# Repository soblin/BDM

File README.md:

Repository for development of "Electrical Informtion Processing Devices"

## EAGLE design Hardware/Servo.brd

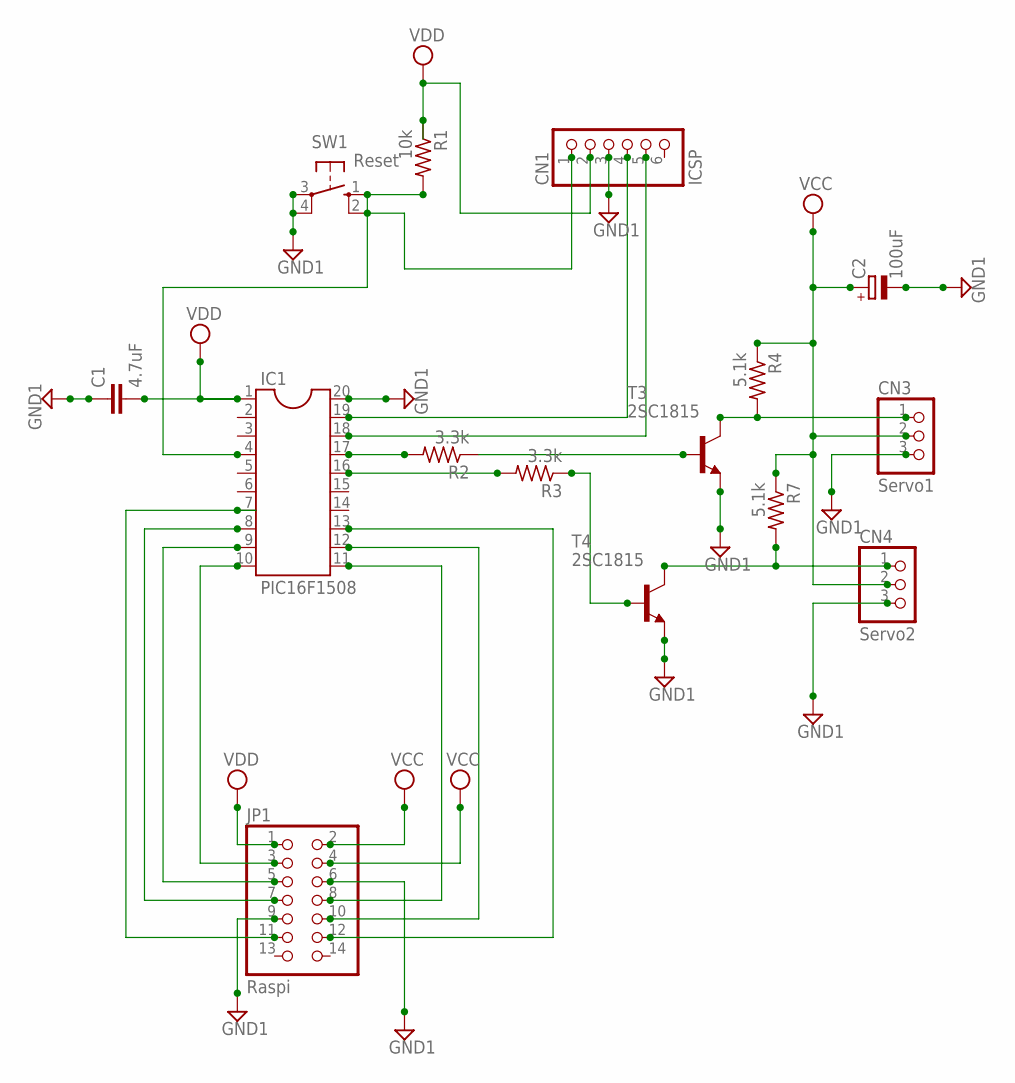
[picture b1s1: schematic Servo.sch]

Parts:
C1: 4.7uF; C025-025X050
C2: 100uF; PANASONIC_A
CN1: ICSP; 1X06
CN3: Servo1; 1X03
CN4: Servo2; 1X03
IC1: PIC16F1508; SOCKET-20
JP1: Raspi; 2X07
R1: 10k; V526-0
R2, R3: 3.3k; V526-0
R4, R7: 5.1k; V526-0
SW1: Reset; B3F-10XX
T3, T4: 2SC1815; TO92-ECB

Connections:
GND1: C1.1, C2.-, CN1.3, CN3.3, CN4.3, IC1.20, JP1.6, JP1.9, SW1.3, SW1.4 (P1), T3.E, T4.E
unnamed: IC1.10, JP1.3
unnamed: IC1.9, JP1.5
unnamed: IC1.8, JP1.7
unnamed: CN4.1, R7.2, T4.C
unnamed: IC1.7, JP1.11
unnamed: IC1.11, JP1.8
unnamed: IC1.12, JP1.10
unnamed: CN1.1, IC1.4, R1.2, SW1.1 (S), SW1.2 (S1)
unnamed: IC1.13, JP1.12
unnamed: IC1.17, R2.2
unnamed: IC1.16, R3.2
unnamed: R2.1, T3.B
unnamed: R3.1, T4.B
unnamed: CN3.1, R4.2, T3.C
unnamed: CN1.4, IC1.19
unnamed: CN1.5, IC1.18
VCC: C2.+, CN3.2, CN4.2, JP1.2, JP1.4, R4.1, R7.1
VDD: C1.2, CN1.2, IC1.1, JP1.1, R1.1

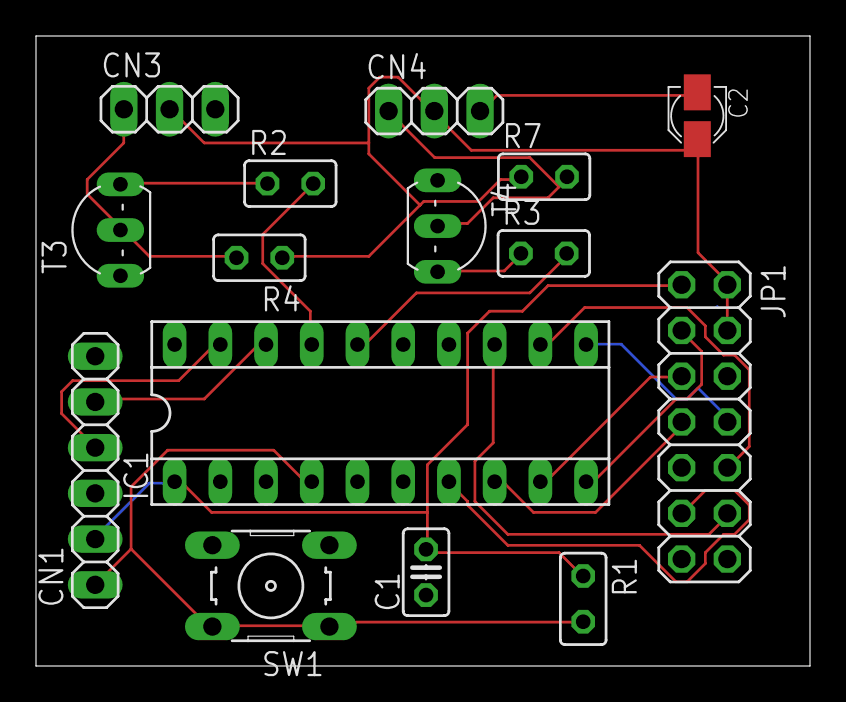
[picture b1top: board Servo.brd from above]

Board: 2 copper layers, 43.0 x 35.0 mm, 15 parts (0 on the bottom side), 19 nets.

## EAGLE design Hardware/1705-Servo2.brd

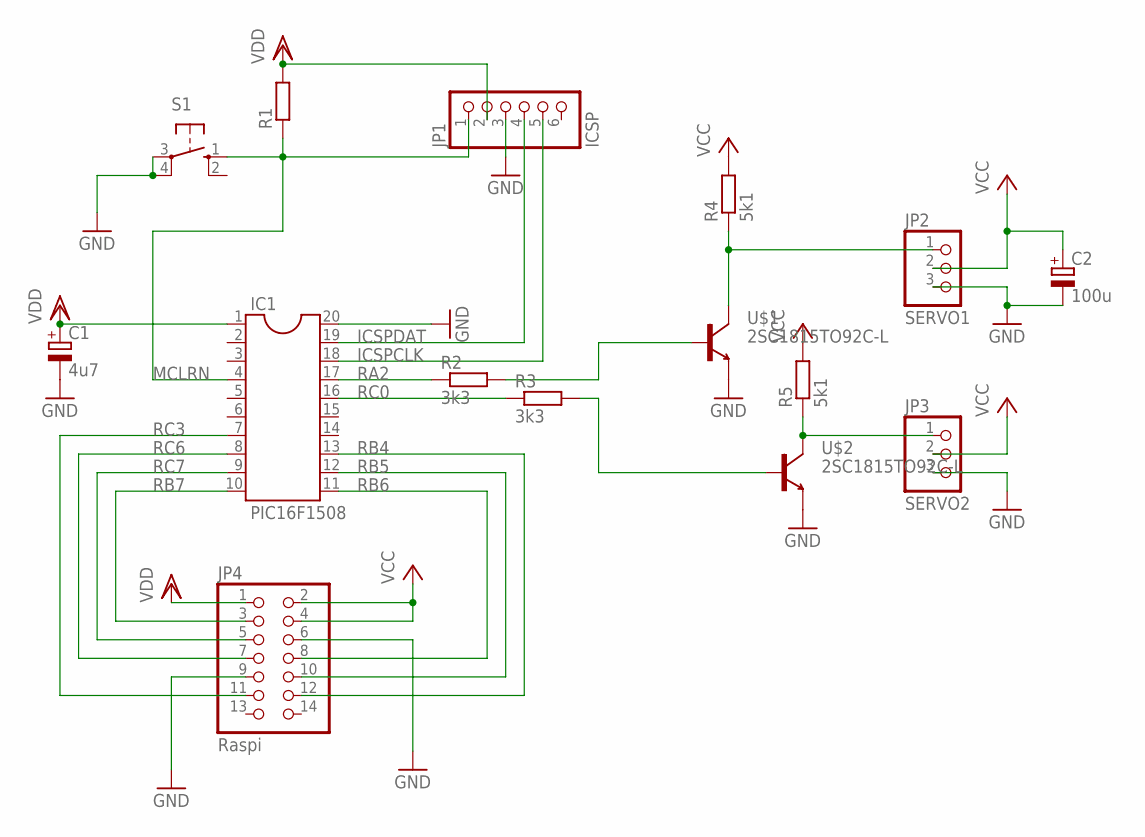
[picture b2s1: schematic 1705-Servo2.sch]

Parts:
C1: 4u7; E5-6E
C2: 100u; E2,5-6E
IC1: PIC16F1508; DIL20
JP1: ICSP; 1X06
JP2: SERVO1; 1X03
JP3: SERVO2; 1X03
JP4: Raspi; 2X07
R1: R-EU_0207/2V; 0207/2V
R2, R3: 3k3; 0204/8
R4, R5: 5k1; 0207/2V
S1: 10-XX; B3F-10XX
U$1, U$2: 2SC1815TO92C-L; TO92C-L

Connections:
GND: C1.-, C2.-, IC1.20, JP1.3, JP2.3, JP3.3, JP4.6, JP4.9, S1.3, S1.4 (P1), U$1.1 (E), U$2.1 (E)
ICSPCLK: IC1.18, JP1.5
ICSPDAT: IC1.19, JP1.4
MCLRN: IC1.4, JP1.1, R1.1, S1.1 (S)
unnamed: JP2.1, R4.1, U$1.2 (C)
unnamed: JP3.1, R5.1, U$2.2 (C)
unnamed: R2.2, U$1.3 (B)
unnamed: R3.2, U$2.3 (B)
RA2: IC1.17, R2.1
RB4: IC1.13, JP4.12
RB5: IC1.12, JP4.10
RB6: IC1.11, JP4.8
RB7: IC1.10, JP4.3
RC0: IC1.16, R3.1
RC3: IC1.7, JP4.11
RC6: IC1.8, JP4.7
RC7: IC1.9, JP4.5
VCC: C2.+, JP2.2, JP3.2, JP4.2, JP4.4, R4.2, R5.2
VDD: C1.+, IC1.1, JP1.2, JP4.1, R1.2

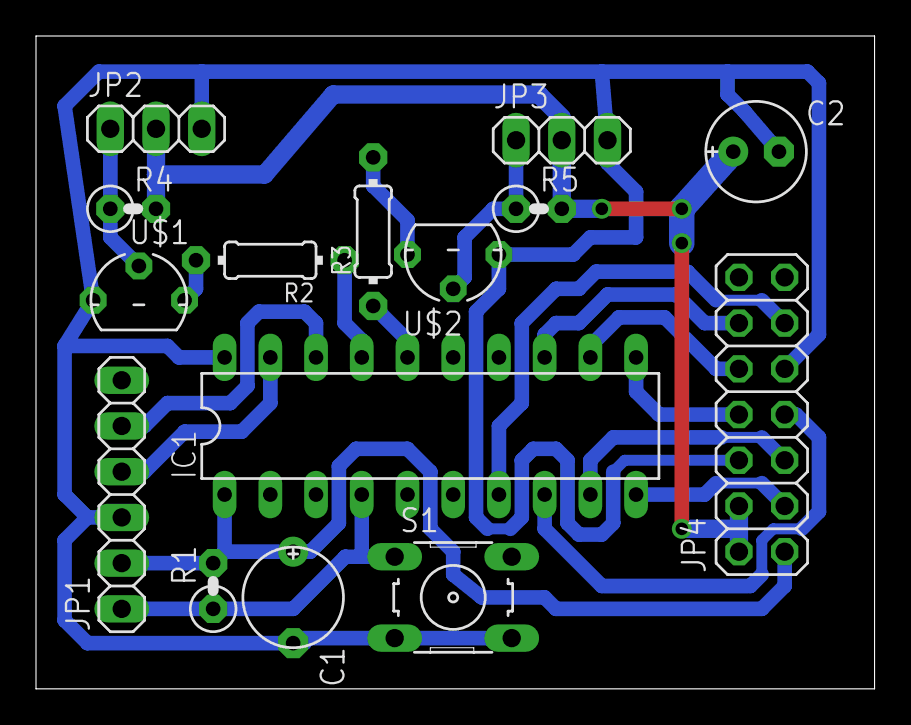
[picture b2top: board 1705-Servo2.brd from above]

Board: 2 copper layers, 46.6 x 36.3 mm, 15 parts (0 on the bottom side), 19 nets.

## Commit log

2017-12-06 initialize
2017-12-06 Added readme
2017-12-06 RemoteControl.py
2018-01-12 1/12
